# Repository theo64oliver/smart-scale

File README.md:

# **Rapport Technique**

Ce projet a ete effectue en groupe de 4 sur une duree de 2 semaines, compose de Antoine JOUY, Alexis VASSEUR, Benjamin BOYER et Theo OLIVER.

## **1. Calcul de résistance :**

### **Buzzer :**

* Le buzzer doit être alimenté en **5 V**.
* Le courant ne doit pas dépasser **30 mA**.
* Choix d’un courant de fonctionnement de **15 mA**.

Utilisation de la loi d’Ohm :

$$
V = R \times I \Rightarrow R = \frac{V}{I} = \frac{5}{0{,}015} = 333\ \Omega
$$

**Résistance à ajouter pour le buzzer : 333 Ω**

**Choix pratique : résistance normalisée de 330 Ω**

Calcul de la puissance :

$$
P = I^2 \times R = (0{,}015)^2 \times 330 = 0.07425\,W
$$

**Dissipation thermique : environ 74,2 mW**

---

## **2. Boutons poussoirs**

### **Résistances de pull-down :**

* Choix d’une résistance de **10 kΩ** (valeur courante).
* Ce choix permet un compromis entre la stabilité du signal et la vitesse de réponse du filtre.
* Objectif : gestion du rebond (debounce) entre **20 ms et 50 ms**.

#### **Dissipation thermique :**

Calcul du courant :

$$
I = \frac{V}{R} = \frac{3{,}3}{10000} = 0{,}00033\,A = 0{,}33\,mA
$$

Calcul de la puissance :

$$
P = I^2 \times R = (0{,}00033)^2 \times 10000 = 0{,}001089\,W
$$

**Dissipation thermique : environ 1,1 mW**

---

### **Condensateurs pour anti-rebond (filtre RC)**

Objectif : obtenir une constante de temps $\tau$ d’environ **6,67 ms** (20 ms ÷ 3)

$$
C = \frac{\tau}{R} = \frac{0{,}00667}{10000} = 667 \times 10^{-9}\,F = 667\,nF
$$

**Valeur normalisée à utiliser : 680 nF**

---

## **3. LED connectée au GPIO 17**

* Tension du GPIO : **3,3 V**
* Tension typique d’une LED rouge : **Vled ≈ 2,0 V**
* Courant souhaité : **I = 5 à 20 mA** (choix : 15 mA)

Calcul de la tension aux bornes de la résistance :

$$
V_R = V_{GPIO} - V_{LED} = 3{,}3 - 2{,}0 = 1{,}3\,V
$$

Calcul de la résistance :

$$
R = \frac{V_R}{I} = \frac{1{,}3}{0{,}015} ≈ 87\,\Omega
$$

**Choix pratique : résistance normalisée de 100 Ω pour réduire le courant.**

### **Dissipation thermique de la résistance :**

Avec R = 100 Ω et I = 15 mA :

$$
P = I^2 \times R = (0{,}015)^2 \times 100 = 0{,}000225 \times 100 = 0{,}0225\,W = 22{,}5\,mW
$$

**Dissipation thermique : environ 22,5 mW (très faible, standard acceptable)**

---

## **4. Alimentation (régulateur 7805)**

### **Condensateurs :**

* Utilisation de **2 condensateurs céramiques** recommandée avec le régulateur **7805** :

  * Un **condensateur de 0,33 µF** en entrée
  * Un **condensateur de 0,1 µF** en sortie

Source : [Analyse du 7805](https://www.ic-components.fr/blog/comprehensive-analysis-and-applications-of-the-7805-voltage-regulator-ic.jsp)

## **Commentaires**

### Choix techniques  
Nous avons choisi de ne pas inclure d’emplacements pour le capteur de pression et l’écran LCD sur le PCB. Cette décision a été motivée par la volonté de réduire au maximum la surface du circuit imprimé, afin de limiter les coûts de fabrication.  
Voici notre vision de la balance :

Concernant la LED d’alimentation, nous avons opté pour une implémentation matérielle simple. Le détail de ce choix est visible dans le schéma d’alimentation.

### BOM  
La nomenclature des composants (BOM) est disponible dans l’archive ZIP fournie. Nous avons volontairement choisi de ne pas indiquer les prix exacts, car ceux-ci peuvent varier entre le moment de la rédaction et l’achat effectif des composants.

### Rapport DRC  
Lors de la conception du PCB, nous avons pris soin de consulter le rapport DRC (Design Rule Check) afin de nous assurer qu’aucune erreur de routage n’était présente. Le résultat final ne présente aucune erreur : le PCB est conforme aux règles de conception.

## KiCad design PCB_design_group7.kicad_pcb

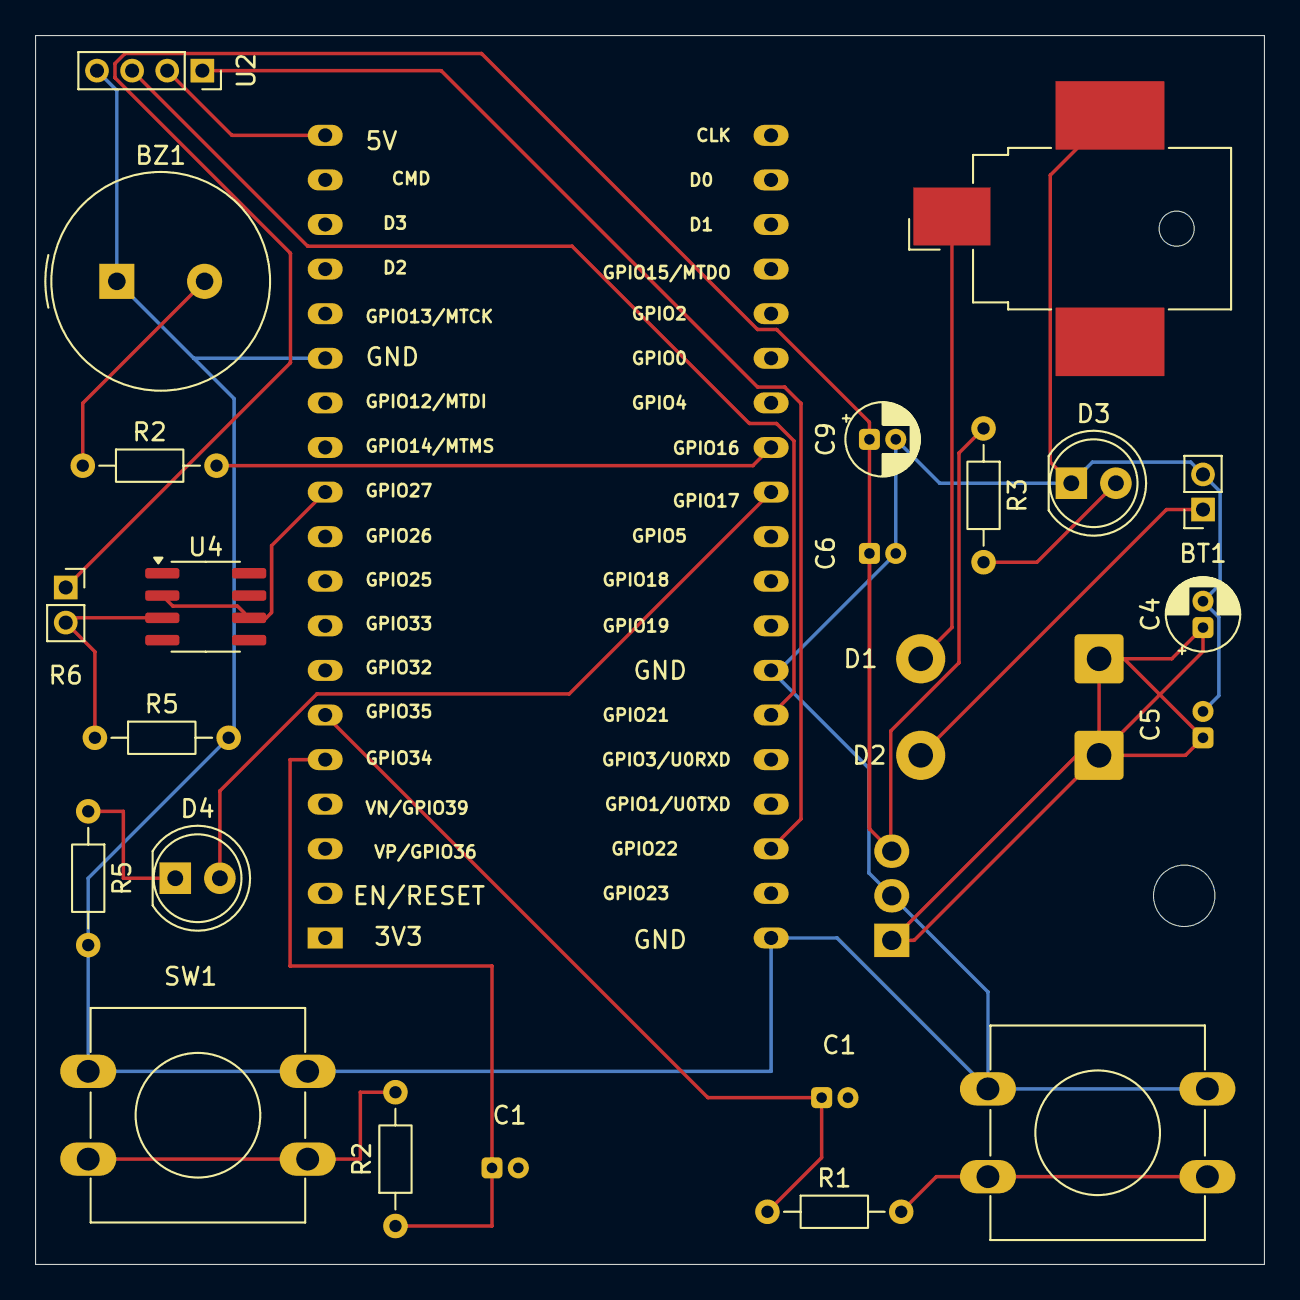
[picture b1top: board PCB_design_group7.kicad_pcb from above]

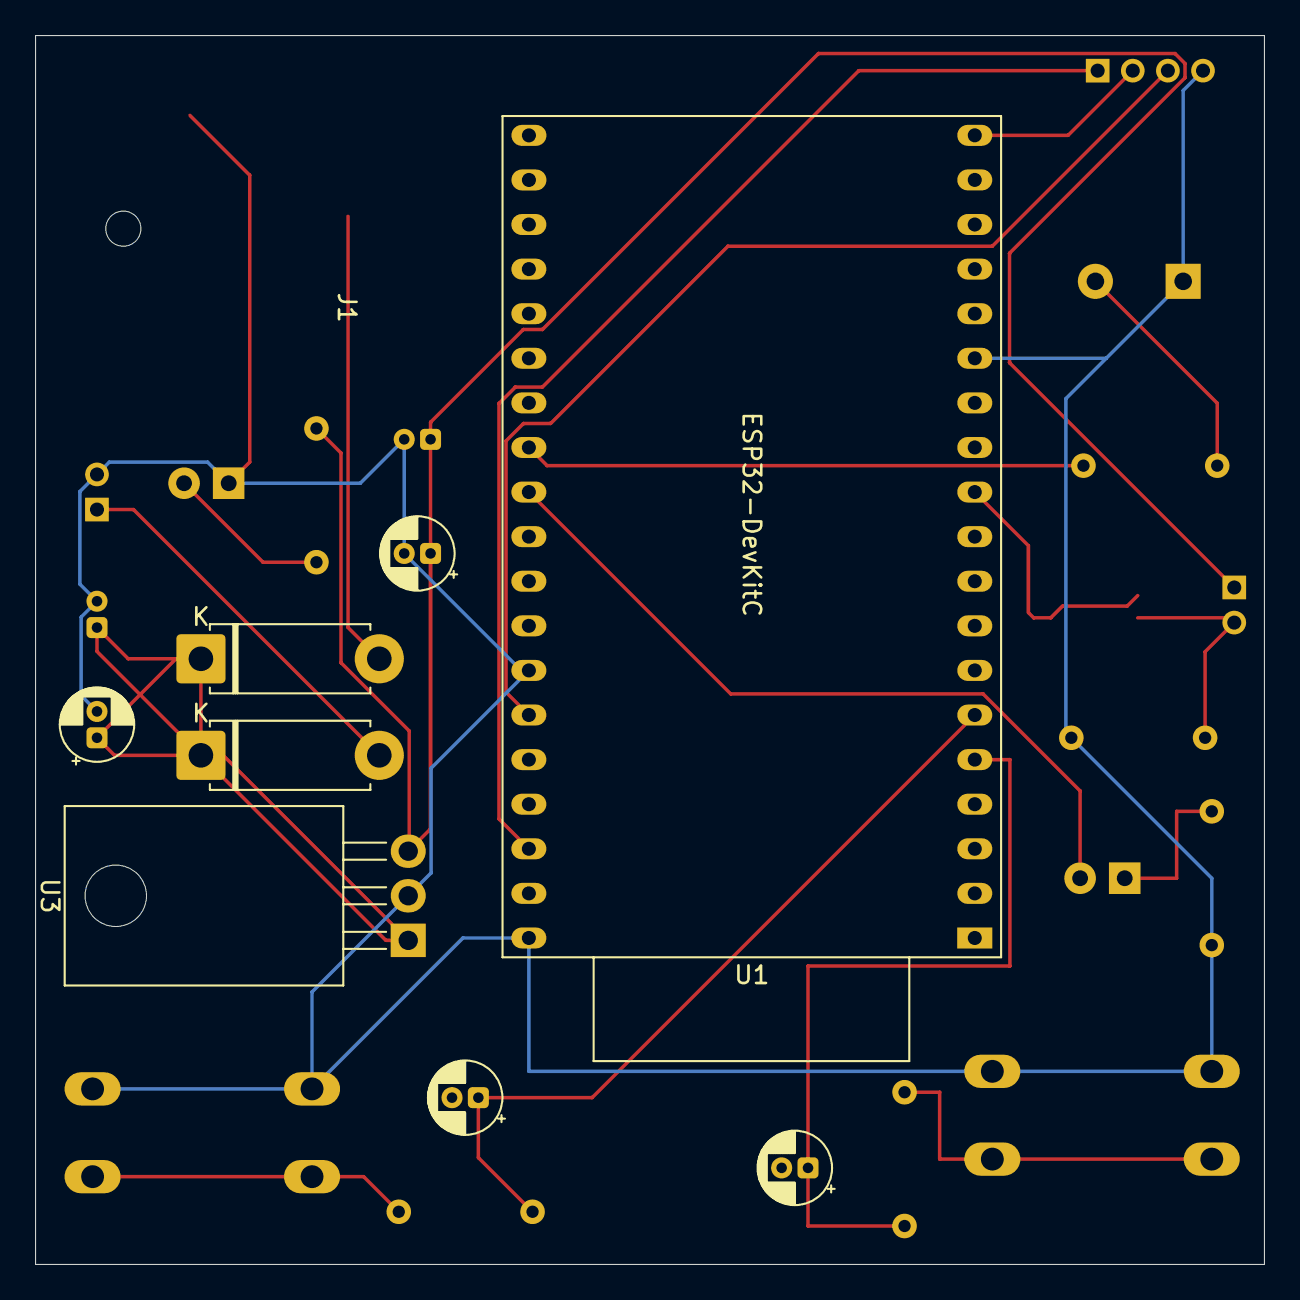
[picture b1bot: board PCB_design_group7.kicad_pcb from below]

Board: 2 copper layers, 70.0 x 70.0 mm, 26 parts (8 on the bottom side), 19 nets.

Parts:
BT1: Battery; PinSocket_1x02_P2.00mm_Vertical
BZ1: Buzzer; Buzzer_TDK_PS1240P02BT_D12.2mm_H6.5mm
C1, C1#2: 680nF; CP_Radial_D4.0mm_P1.50mm
C4, C9: 10µF; CP_Radial_D4.0mm_P1.50mm
C5, C6: 100nF; CP_Radial_D4.0mm_P1.50mm
D1, D2: D; D_5W_P10.16mm_Horizontal
D3, D4: LED; LED_D5.0mm
J1: Barrel_Jack_Switch_Pin3Ring; BarrelJack_CUI_PJ-036AH-SMT_Horizontal
R1, R2: 10kΩ; R_Axial_DIN0204_L3.6mm_D1.6mm_P7.62mm_Horizontal
R2#2, R5#2: 330Ω; R_Axial_DIN0204_L3.6mm_D1.6mm_P7.62mm_Horizontal
R3, R5: 220Ω; R_Axial_DIN0204_L3.6mm_D1.6mm_P7.62mm_Horizontal
R6: X; PinSocket_1x02_P2.00mm_Vertical
SW1, SW2: SW_Push; SW_PUSH-12mm
U1: ESP32-DevKitC
U2: LCD-016N002L; PinSocket_1x04_P2.00mm_Vertical
U3: LM7805_TO220; TO-220-3_Horizontal_TabDown
U4: OP1177AR; SOIC-8_3.9x4.9mm_P1.27mm

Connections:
+5V: U1.19 (5V), U2.2 (VDD)
+5VD: C6.1, C9.1, R3.1, R6.1, U3.3 (VO)
/Bouton Tare/GPIO 34: R2.2, SW1.2
/Bouton Valider Tarage/GPIO 35: R1.2, SW2.2
/GPIO 16: R2#2.2, U1.27 (GPIO16)
/GPIO 17: D4.2 (A), U1.28 (GPIO17)
/GPIO 21: U1.33 (GPIO21), U2.3 (VO)
/GPIO 22: U1.36 (GPIO22), U2.1 (VSS)
/GPIO 27: U1.11 (ADC2_CH7/GPIO27), U4.2 (-), U4.6
/GPIO 34: C1#2.1, R2.1, U1.5 (VDET_1/GPIO34/ADC1_CH6)
/GPIO 35: C1.1, R1.1, U1.6 (VDET_2/GPIO35/ADC1_CH7)
GND: BT1.2 (-), BZ1.1 (+), C4.2, C5.2, C6.2, C9.2, D3.1 (K), J1.3, R5.2, R5#2.2, SW1.1, SW2.1, U1.14 (GND), U1.32 (GND), U1.38 (GND), U2.4 (RS), U3.2 (GND)
unnamed: BT1.1 (+), D2.2 (A)
unnamed: BZ1.2 (-), R2#2.1
unnamed: D1.2 (A), J1.1
unnamed: C4.1, C5.1, D1.1 (K), D2.1 (K), U3.1 (VI)
unnamed: D3.2 (A), R3.2
unnamed: D4.1 (K), R5.1
unnamed: R5#2.1, R6.2, U4.3 (+)

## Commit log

2025-08-21 feat: Add pcb + schematic files. Add readme to explain all choices.
